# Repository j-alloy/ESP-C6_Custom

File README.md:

# ESP-C6_Custom
To develop a Custom ESP32-C6 for study

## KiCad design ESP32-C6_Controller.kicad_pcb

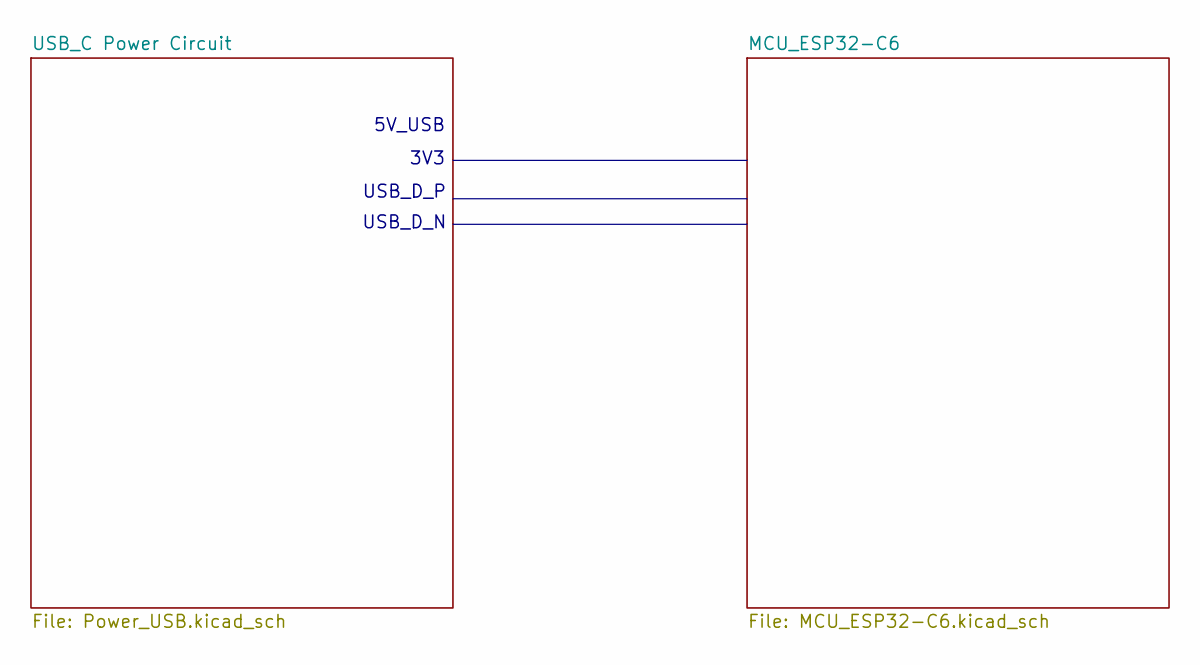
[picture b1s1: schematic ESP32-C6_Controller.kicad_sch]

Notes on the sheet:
USB_D_P
3V3
5V_USB
USB_D_N

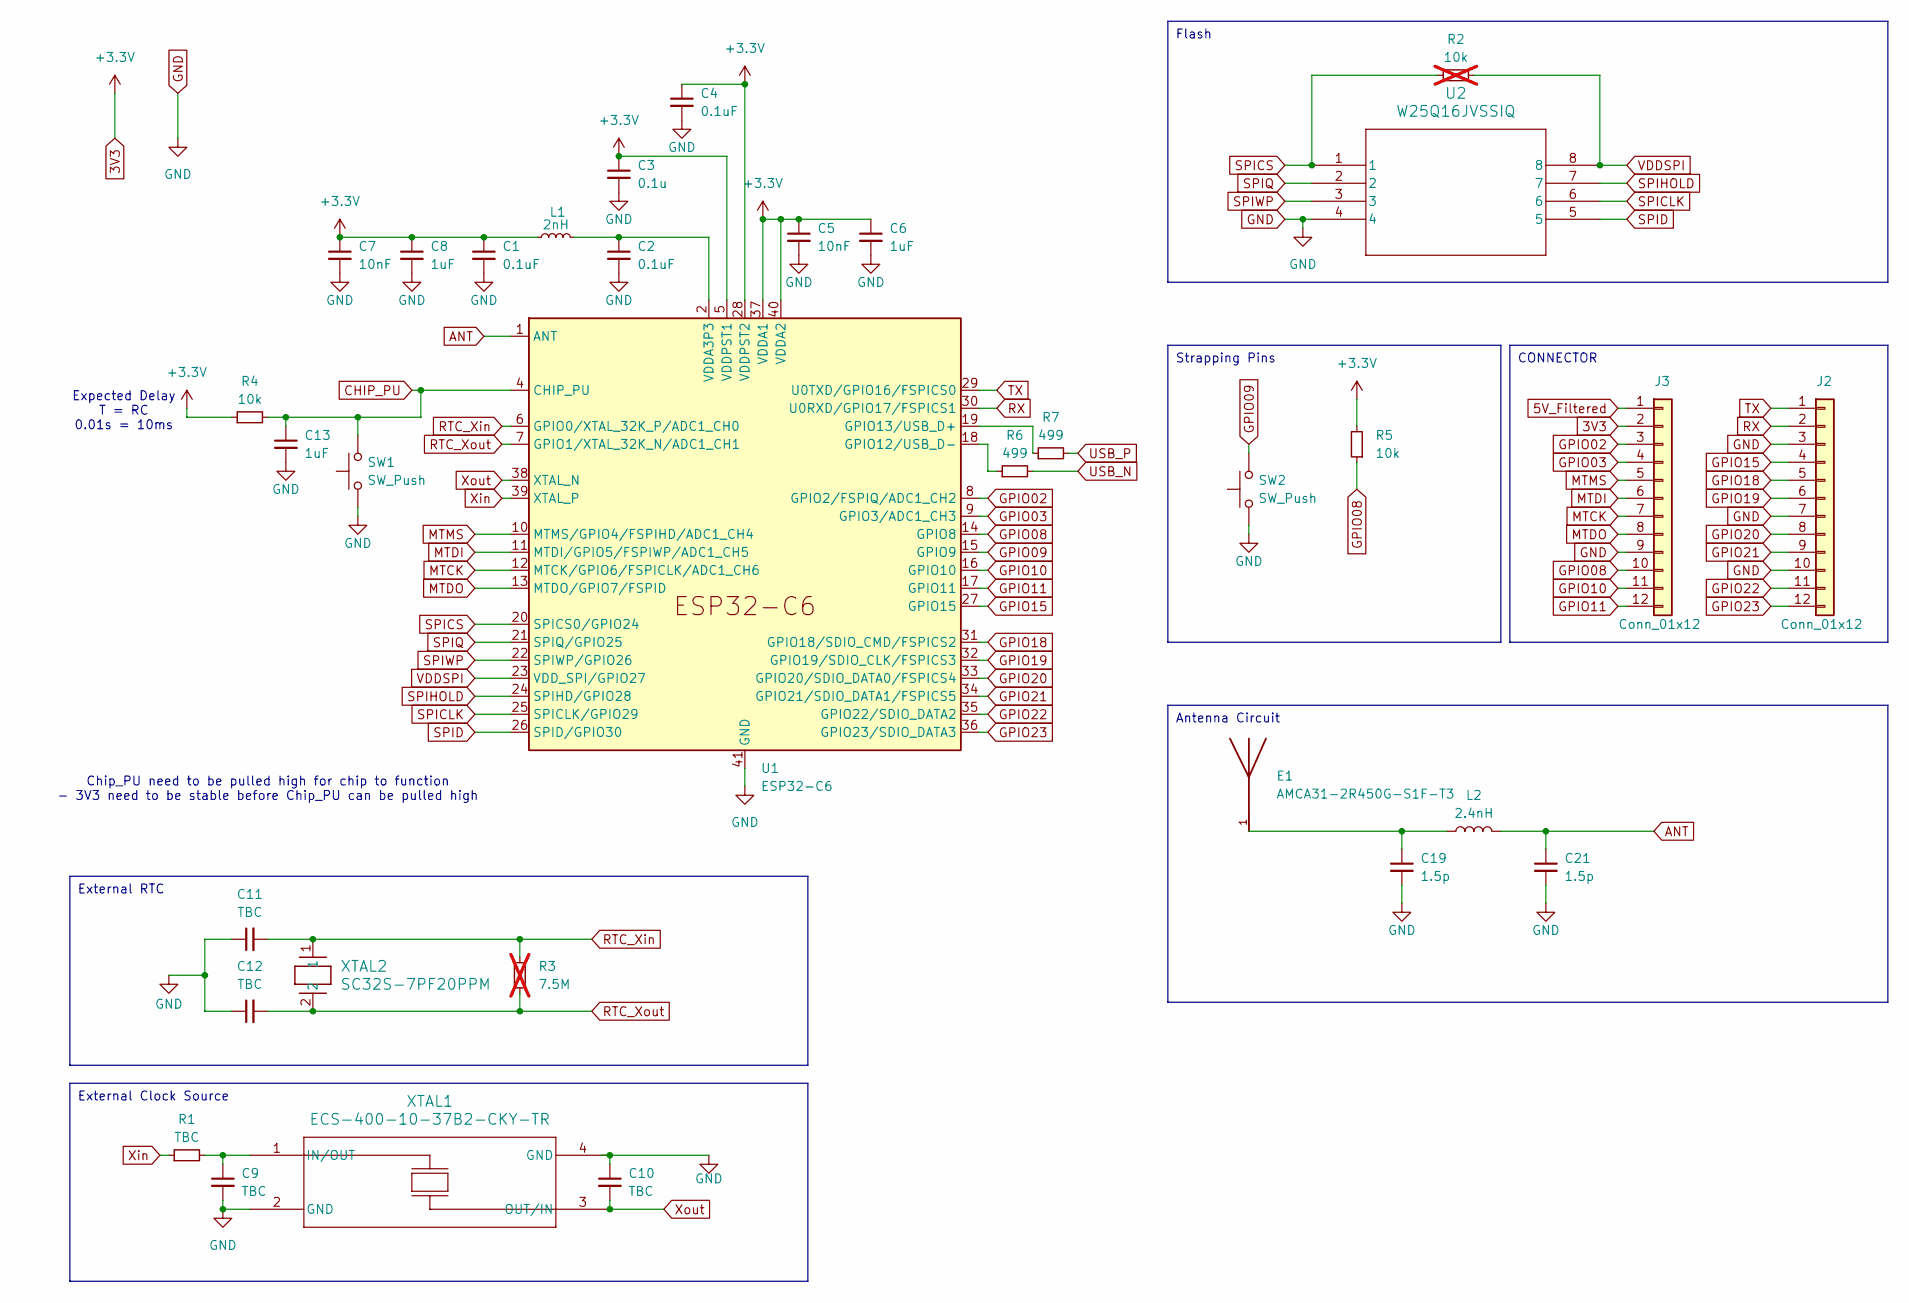
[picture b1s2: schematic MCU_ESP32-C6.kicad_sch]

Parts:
C1, C2, C4: 0.1uF; C_0402_1005Metric
C3: 0.1u; C_0402_1005Metric
C5, C7: 10nF; C_0402_1005Metric
C6, C8, C13: 1uF; C_0402_1005Metric
C9, C10, C11, C12: TBC; C_0603_1608Metric
C19, C21: 1.5p; C_0603_1608Metric
E1: AMCA31-2R450G-S1F-T3; XDCR_AMCA31-2R450G-S1F-T3; PARTREV 03-21-19
J2, J3: Conn_01x12; PinSocket_1x12_P2.54mm_Vertical
L1: 2nH; L_0805_2012Metric
L2: 2.4nH; L_0805_2012Metric
R1: TBC; R_0402_1005Metric
R2: 10k; R_0402_1005Metric; not fitted
R3: 7.5M; R_0402_1005Metric; not fitted
R4, R5: 10k; R_0402_1005Metric
R6, R7: 499; R_0402_1005Metric
SW1, SW2: SW_Push; SW4_PTS815 SJM 250 SMTR LFS_CNK
U1: ESP32-C6; QFN-40-1EP_5x5mm_P0.4mm_EP3.6x3.6mm
U2: W25Q16JVSSIQ; W25Q16JVSSIQ_WIN
XTAL1: ECS-400-10-37B2-CKY-TR; ECX-1637B2_ECS
XTAL2: SC32S-7PF20PPM; XTAL_SC32S-7PF20PPM_EPS

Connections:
3V3: C1.1, C3.1, C4.1, C5.1, C6.1, C7.1, C8.1, J3.2, L1.1, R4.1, R5.2, U1.5 (VDDPST1), U1.28 (VDDPST2), U1.37 (VDDA1), U1.40 (VDDA2); also elsewhere on the board
5V_Filtered: J3.1; also elsewhere on the board
ANT: C21.1, L2.2, U1.1 (ANT)
CHIP_PU: C13.1, R4.2, SW1.2, U1.4 (CHIP_PU)
DN1: R6.2; also elsewhere on the board
DP1: R7.2; also elsewhere on the board
GND: C1.2, C2.2, C3.2, C4.2, C5.2, C6.2, C7.2, C8.2, C9.2, C10.1, C11.1, C12.1, C13.2, C19.2, C21.2, J2.3, J2.7, J2.10, J3.9, SW1.1, SW2.1, U1.41 (GND), U2.4, XTAL1.2 (GND), XTAL1.4 (GND); also elsewhere on the board
GPIO02: J3.3, U1.8 (GPIO2/FSPIQ/ADC1_CH2)
GPIO03: J3.4, U1.9 (GPIO3/ADC1_CH3)
GPIO08: J3.10, R5.1, U1.14 (GPIO8)
GPIO09: SW2.2, U1.15 (GPIO9)
GPIO10: J3.11, U1.16 (GPIO10)
GPIO11: J3.12, U1.17 (GPIO11)
GPIO15: J2.4, U1.27 (GPIO15)
GPIO18: J2.5, U1.31 (GPIO18/SDIO_CMD/FSPICS2)
GPIO19: J2.6, U1.32 (GPIO19/SDIO_CLK/FSPICS3)
GPIO20: J2.8, U1.33 (GPIO20/SDIO_DATA0/FSPICS4)
GPIO21: J2.9, U1.34 (GPIO21/SDIO_DATA1/FSPICS5)
GPIO22: J2.11, U1.35 (GPIO22/SDIO_DATA2)
GPIO23: J2.12, U1.36 (GPIO23/SDIO_DATA3)
MTCK: J3.7, U1.12 (MTCK/GPIO6/FSPICLK/ADC1_CH6)
MTDI: J3.6, U1.11 (MTDI/GPIO5/FSPIWP/ADC1_CH5)
MTDO: J3.8, U1.13 (MTDO/GPIO7/FSPID)
MTMS: J3.5, U1.10 (MTMS/GPIO4/FSPIHD/ADC1_CH4)
unnamed: C2.1, L1.2, U1.2 (VDDA3P3), U1.3 (VDDA3P3)
unnamed: C19.1, E1.1, L2.1
unnamed: R6.1, U1.18 (GPIO12/USB_D-)
unnamed: R7.1, U1.19 (GPIO13/USB_D+)
unnamed: C9.1, R1.2, XTAL1.1 (IN/OUT)
RTC_Xin: C11.2, R3.2, U1.6 (GPIO0/XTAL_32K_P/ADC1_CH0), XTAL2.1
RTC_Xout: C12.2, R3.1, U1.7 (GPIO1/XTAL_32K_N/ADC1_CH1), XTAL2.2
RX: J2.2, U1.30 (U0RXD/GPIO17/FSPICS1)
SPICLK: U1.25 (SPICLK/GPIO29), U2.6
SPICS: R2.1, U1.20 (SPICS0/GPIO24), U2.1
SPID: U1.26 (SPID/GPIO30), U2.5
SPIHOLD: U1.24 (SPIHD/GPIO28), U2.7
SPIQ: U1.21 (SPIQ/GPIO25), U2.2
SPIWP: U1.22 (SPIWP/GPIO26), U2.3
TX: J2.1, U1.29 (U0TXD/GPIO16/FSPICS0)
VDDSPI: R2.2, U1.23 (VDD_SPI/GPIO27), U2.8
Xin: R1.1, U1.39 (XTAL_P)
Xout: C10.2, U1.38 (XTAL_N), XTAL1.3 (OUT/IN)

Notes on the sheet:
Strapping Pins
Flash
CONNECTOR
External RTC
External Clock Source
Antenna Circuit
Chip_PU need to be pulled high for chip to function - 3V3 need to be stable before Chip_PU can be pulled high
Expected Delay T = RC 0.01s = 10ms

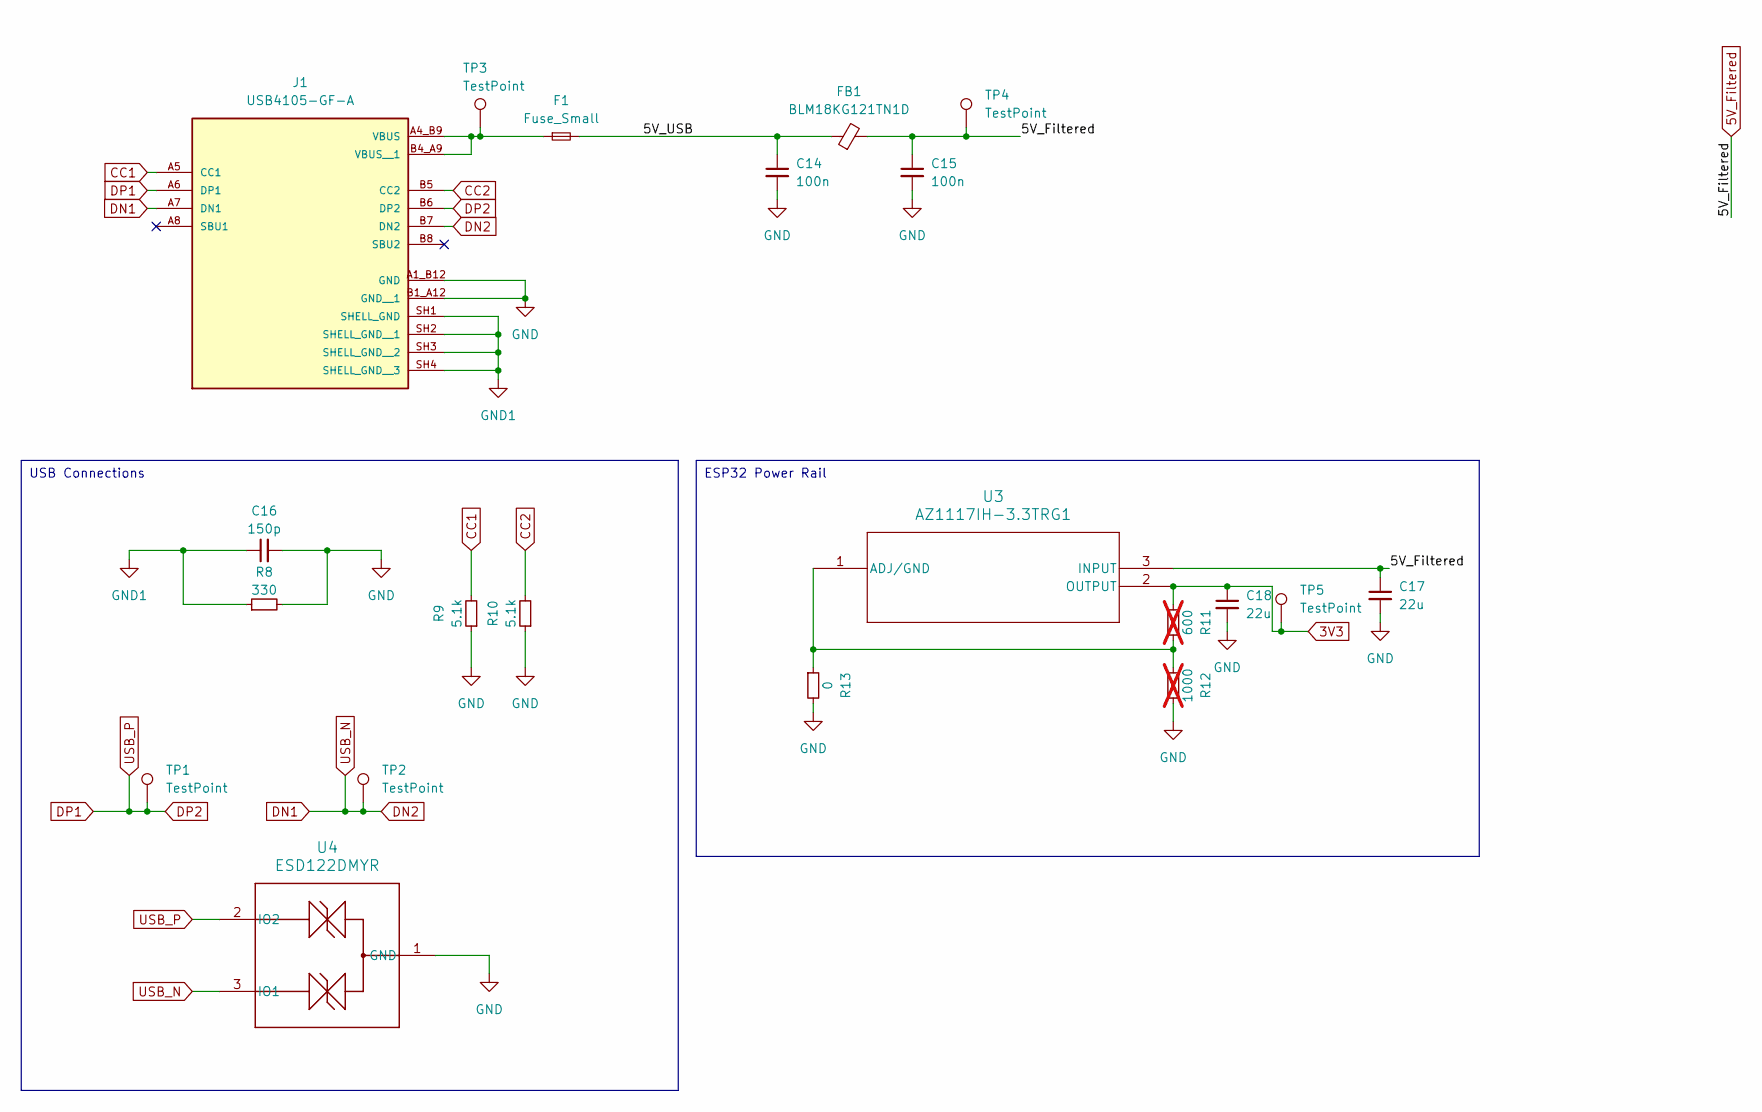
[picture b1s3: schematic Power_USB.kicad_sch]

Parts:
C14, C15: 100n; C_0402_1005Metric
C16: 150p; C_0603_1608Metric
C17, C18: 22u; C_0805_2012Metric
F1: Fuse_Small; Fuse_1206_3216Metric
FB1: BLM18KG121TN1D; L_CommonModeChoke_Coilcraft_0603USB
J1: USB4105-GF-A; GCT_USB4105-GF-A; PARTREV B3
R8: 330; R_0603_1608Metric
R9, R10: 5.1k; R_0603_1608Metric
R11: 600; R_0402_1005Metric; not fitted
R12: 1000; R_0402_1005Metric; not fitted
R13: 0; R_0402_1005Metric
TP1, TP2, TP3, TP4, TP5: TestPoint; TestPoint_Pad_1.5x1.5mm
U3: AZ1117IH-3.3TRG1; SOT223_AZ1117I_6P5X3P5_DIO
U4: ESD122DMYR; DMY0003A

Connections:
3V3: C18.1, R11.1, TP5.1, U3.2 (OUTPUT); also elsewhere on the board
5V_Filtered: C15.1, C17.1, FB1.2, TP4.1, U3.3 (INPUT); also elsewhere on the board
/USB_C Power Circuit/5V_USB: C14.1, F1.2, FB1.1
CC1: J1.A5 (CC1), R9.2
CC2: J1.B5 (CC2), R10.2
DN1: J1.A7 (DN1), J1.B7 (DN2), TP2.1, U4.3 (IO1); also elsewhere on the board
DP1: J1.A6 (DP1), J1.B6 (DP2), TP1.1, U4.2 (IO2); also elsewhere on the board
GND: C14.2, C15.2, C16.2, C17.2, C18.2, J1.A1_B12 (GND), J1.B1_A12 (GND__1), R8.2, R9.1, R10.1, R12.2, R13.2, U4.1 (GND); also elsewhere on the board
GND1: C16.1, J1.SH1 (SHELL_GND), J1.SH2 (SHELL_GND__1), J1.SH3 (SHELL_GND__2), J1.SH4 (SHELL_GND__3), R8.1
unnamed: F1.1, J1.A4_B9 (VBUS), J1.B4_A9 (VBUS__1), TP3.1
unnamed: R11.2, R12.1, R13.1, U3.1 (ADJ/GND)

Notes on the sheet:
ESP32 Power Rail
USB Connections

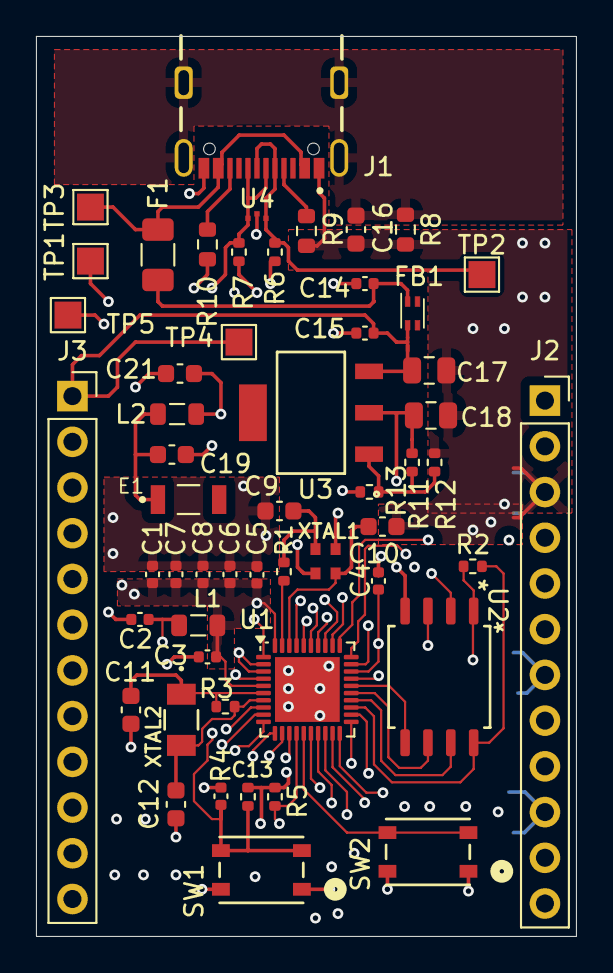
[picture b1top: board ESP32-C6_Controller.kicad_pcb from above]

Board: 6 copper layers, 30.0 x 50.0 mm, 54 parts (0 on the bottom side), 48 nets.

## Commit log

2024-06-30 -add fuse -change connectors footprint - push button footprint changed
2024-09-01 - Change Copper Layer from 2 to 4
2024-09-01 import components
2024-09-01 add gitignore
2024-09-01 Layout update positions
2024-09-02 4 layer to 6 layer
2024-09-02 Put components inside the board
2024-09-02 Final position before routing
2024-09-02 layout 80% done
2024-09-02 Trace completed, leave comments for tasks
2024-09-03 add comment to add fiducials
2025-02-23 fix unconnected and plane
